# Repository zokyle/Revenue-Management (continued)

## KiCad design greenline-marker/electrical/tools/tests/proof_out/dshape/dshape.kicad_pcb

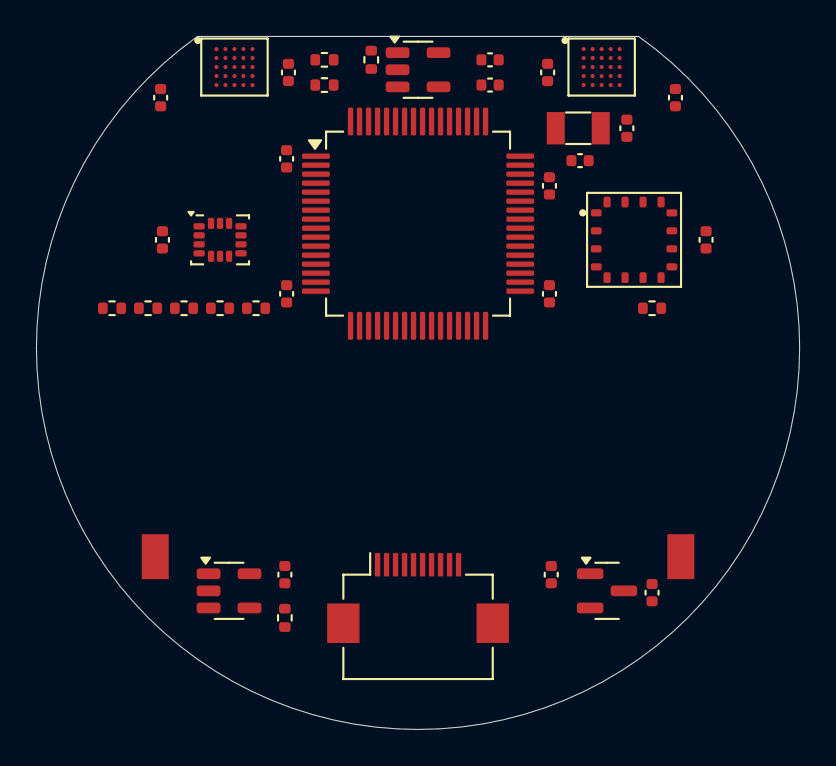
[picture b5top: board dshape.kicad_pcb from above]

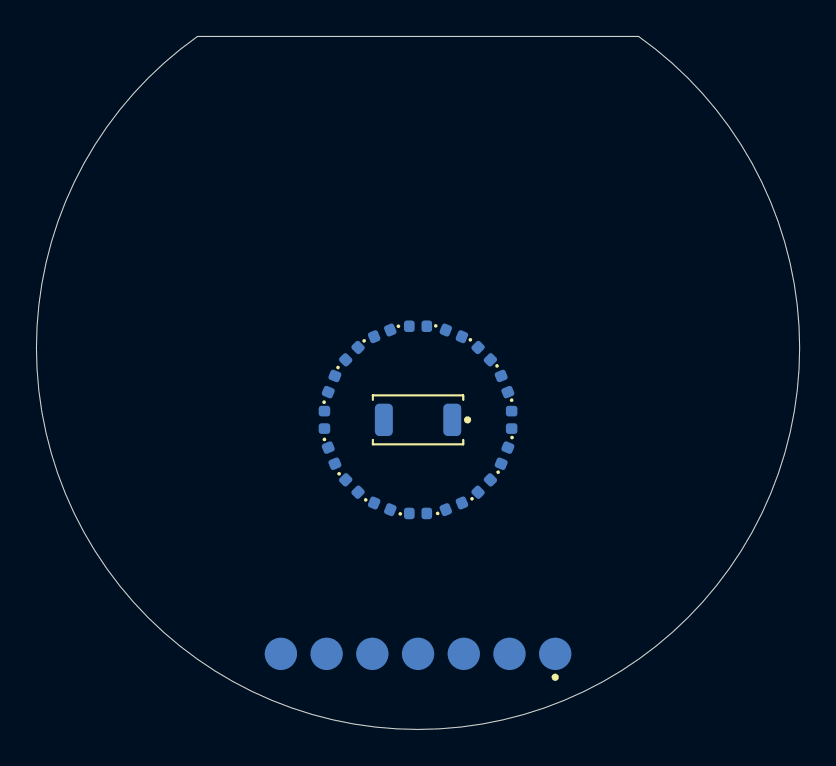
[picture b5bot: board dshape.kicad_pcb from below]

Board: 4 copper layers, 42.4 x 38.5 mm, 57 parts (18 on the bottom side), 56 nets, no tracks yet.

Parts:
BT1: BAT+; BatteryTab_1.5x2.5mm
BT2: BAT-; BatteryTab_1.5x2.5mm
C1, C2, C3, C12, C13, C16, C17: 100n; C_0402_1005Metric
C4: 4u7; C_0402_1005Metric
C5, C6, C7, C8, C9, C10, C11: 1u; C_0402_1005Metric
C14, C15: 12p; C_0402_1005Metric
D1, D3, D5, D7, D9, D11, D13, D15: LED red; LED_0402_1005Metric
D2, D4, D6, D8, D10, D12, D14, D16: LED NIR; LED_0402_1005Metric
J1: LCD FPC 10; Hirose_FH12-10S-0.5SH_1x10-1MP_P0.50mm_Horizontal
J2: Cradle pads; ContactRow_7x1.8mm_P2.54
PD1: Photodiode; Photodiode_4.8x2.5mm
R1, R2, R3, R4, R5: 68R; R_0402_1005Metric
R6, R7, R10: 2k2; R_0402_1005Metric
R8: 49k9; R_0402_1005Metric
R9: 100k; R_0402_1005Metric
U1: MCU LQFP-64; LQFP-64_10x10mm_P0.5mm
U2, U3: Camera cube; CamCube_BGA25_P0.5
U4: IMU LGA-14; LGA-14_3x2.5mm_P0.5mm_LayoutBorder3x4y
U5: Inclinometer LGA-16; LGA-16_5x5mm_P1.0mm
U7: LDO 3V0; SOT-23
U8: LDO 2V8; SOT-23-5
U9: Charger; SOT-23-5
Y1: 32.768k; Crystal_SMD_3215-2Pin_3.2x1.5mm

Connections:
+3V0: C1.1, C2.1, C3.1, C4.1, C11.1, C12.1, C13.1, J1.6, J1.7, J1.8, U1.1 (VDD), U1.19 (VDD), U1.32 (VDD), U1.48 (VDD), U1.64 (VDD), U4.5 (VDDIO), U4.8 (VDD), U5.1 (VDD), U5.2 (VDDIO), U7.2 (VOUT)
CAM_D0: U1.50 (D0), U2.B2 (D0), U3.B2 (D0)
CAM_D1: U1.51 (D1), U2.B3 (D1), U3.B3 (D1)
CAM_D2: U1.52 (D2), U2.B4 (D2), U3.B4 (D2)
CAM_D3: U1.53 (D3), U2.C2 (D3), U3.C2 (D3)
CAM_D4: U1.54 (D4), U2.C3 (D4), U3.C3 (D4)
CAM_D5: U1.55 (D5), U2.C4 (D5), U3.C4 (D5)
CAM_D6: U1.56 (D6), U2.D2 (D6), U3.D2 (D6)
CAM_D7: U1.57 (D7), U2.D3 (D7), U3.D3 (D7)
CAM_EN: R9.1, U1.44 (CAM_EN), U8.3 (EN)
CAM_HREF: U1.59 (HREF), U2.D4 (HREF), U3.D4 (HREF)
CAM_L_DVDD: C7.1, U2.D5 (DVDD)
CAM_PCLK: U1.58 (PCLK), U2.A2 (PCLK), U3.A2 (PCLK)
CAM_PWDN_L: U1.46 (PWDN_L), U2.C1 (PWDN)
CAM_PWDN_R: U1.45 (PWDN_R), U3.C1 (PWDN)
CAM_R_DVDD: C8.1, U3.D5 (DVDD)
CAM_SCL_L: R6.2, U1.62 (SCL_L), U2.B1 (SCL)
CAM_SCL_R: R7.2, U1.33 (SCL_R), U3.B1 (SCL)
CAM_SDA: R10.2, U1.49 (SDA), U2.B5 (SDA), U3.B5 (SDA)
CAM_VSYNC: U1.60 (VSYNC), U2.A3 (VSYNC), U3.A3 (VSYNC)
CAM_XVCLK: U1.61 (XVCLK), U2.A4 (XVCLK), U3.A4 (XVCLK)
CHG_PROG: R8.1, U9.5 (PROG)
CHG_STAT: U1.40 (CHG_STAT), U9.1 (STAT)
CP1: D1.2 (A), D2.1 (K), D9.1 (K), D10.2 (A), D11.2 (A), D12.1 (K), R1.2
CP1_MCU: R1.1, U1.25 (CP1)
CP2: D1.1 (K), D2.2 (A), D3.2 (A), D4.1 (K), D13.2 (A), D14.1 (K), R2.2
CP2_MCU: R2.1, U1.26 (CP2)
CP3: D3.1 (K), D4.2 (A), D5.2 (A), D6.1 (K), D11.1 (K), D12.2 (A), D15.2 (A), D16.1 (K), R3.2
CP3_MCU: R3.1, U1.27 (CP3)
CP4: D5.1 (K), D6.2 (A), D7.2 (A), D8.1 (K), D13.1 (K), D14.2 (A), R4.2
CP4_MCU: R4.1, U1.28 (CP4)
CP5: D7.1 (K), D8.2 (A), D9.2 (A), D10.1 (K), D15.1 (K), D16.2 (A), R5.2
CP5_MCU: R5.1, U1.29 (CP5)
CS_IMU: U1.5 (CS_IMU), U4.12 (CS)
CS_INC: U1.6 (CS_INC), U5.5 (CS)
GND: BT2.1, C1.2, C2.2, C3.2, C4.2, C5.2, C6.2, C7.2, C8.2, C9.2, C10.2, C11.2, C12.2, C13.2, C14.2, C15.2, C16.2, C17.2, J1.9, J1.10, J1.MP, J2.4, PD1.A, R8.2, R9.2, U1.18 (VSS), U1.31 (VSS), U1.47 (VSS), U1.63 (VSS), U2.E2 (GND1), U2.E3 (GND2), U2.E4 (GND3), U3.E2 (GND1), U3.E3 (GND2), U3.E4 (GND3), U4.2 (SDX), U4.3 (SCX), U4.6 (GND1), U4.7 (GND2), U5.3 (GND1), U5.4 (GND2), U7.1 (GND), U8.2 (GND), U9.2 (VSS)
IMU_INT: U1.7 (IMU_INT), U4.4 (INT1)
LCD_DISP: J1.5, U1.24 (LCD_DISP)
LCD_EXTCOMIN: J1.4, U1.23 (LCD_EXTCOMIN)
LCD_SCLK: J1.1, U1.20 (LCD_SCLK)
LCD_SCS: J1.3, U1.22 (LCD_SCS)
LCD_SI: J1.2, U1.21 (LCD_SI)
NRST: J2.7, U1.36 (NRST)
OSC32_IN: C14.1, U1.8 (OSC32_IN), Y1.1
OSC32_OUT: C15.1, U1.9 (OSC32_OUT), Y1.2
PD_K: PD1.K, U1.30 (PD_IN)
SPI_MISO: U1.4 (SPI_MISO), U4.1 (SDO), U5.8 (MISO)
SPI_MOSI: U1.3 (SPI_MOSI), U4.14 (SDA), U5.7 (MOSI)
SPI_SCK: U1.2 (SPI_SCK), U4.13 (SCL), U5.6 (SCK)
SWCLK: J2.6, U1.35 (SWCLK)
SWDIO: J2.5, U1.34 (SWDIO)
USB_DM: J2.2, U1.37 (USB_DM)
USB_DP: J2.3, U1.38 (USB_DP)
V2V8_CAM: C6.1, C16.1, C17.1, R6.1, R7.1, R10.1, U2.C5 (AVDD), U2.D1 (DOVDD), U3.C5 (AVDD), U3.D1 (DOVDD), U8.5 (VOUT)
VBAT: BT1.1, C5.1, C10.1, U7.3 (VIN), U8.1 (VIN), U9.3 (VBAT)
VBUS: C9.1, J2.1, U1.39 (VBUS_SENSE), U9.4 (VDD)

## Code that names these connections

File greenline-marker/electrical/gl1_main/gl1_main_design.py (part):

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VEMD8080_PAD_SIZE = 0.55

#: PROVISIONAL - every number behind the supply-chain table of NETLIST_NOTES 4.1
#: (cradle USB connector -> fuse -> spring pins -> Schottky D17 -> VBUS_D).
#: None of them was read from a data sheet.  ``charger_vin_min`` is the figure
#: docs/research/power.md records for the BQ2510x ("4.45-6.45 V operating
#: input", marked UNVERIFIED there); what the charger does below it (input
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#: STM32U585RITx in LQFP-64, pad 1 .. 64 (PINDATA; check_pinmap.py compares
#: every row with ST's STM32U585RITx.xml and with the installed KiCad symbol).
MCU_PAD_NAMES = (
    "VBAT PC13 PC14 PC15 PH0 PH1 NRST PC0 PC1 PC2 PC3 VSSA VDDA PA0 PA1 PA2 "
    "PA3 VSS VDD PA4 PA5 PA6 PA7 PC4 PC5 PB0 PB1 PB2 PB10 VCAP VSS VDD "
    "PB12 PB13 PB14 PB15 PC6 PC7 PC8 PC9 PA8 PA9 PA10 PA11 PA12 PA13 VSS VDDUSB "
    "PA14 PA15 PC10 PC11 PC12 PD2 PB3 PB4 PB5 PB6 PB7 PH3 PB8 PB9 VSS VDD").split()
assert len(MCU_PAD_NAMES) == 64


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#:   gl_pins.h), CHANGED (moved from the pin in ``was``; ``reason`` says why)
PINMAP = [
    # ---- camera port: fixed by the DCMI alternate functions (spec, PINDATA) --------------
    ("CAM_D0", "PC6", "CAM_D0", "AF", "DCMI_D0", 10, "none", CAM_OFF, S, None, ""),
    ("CAM_D1", "PC7", "CAM_D1", "AF", "DCMI_D1", 10, "none", CAM_OFF, S, None, ""),
    ("CAM_D2", "PC8", "CAM_D2", "AF", "DCMI_D2", 10, "none", CAM_OFF, S, None, ""),
    ("CAM_D3", "PC9", "CAM_D3", "AF", "DCMI_D3", 4, "none", CAM_OFF, S, None, ""),
    ("CAM_D4", "PC11", "CAM_D4", "AF", "DCMI_D4", 10, "none", CAM_OFF, S, None, ""),
    ("CAM_D5", "PB6", "CAM_D5", "AF", "DCMI_D5", 10, "none", CAM_OFF, S, None, ""),
    ("CAM_D6", "PB8", "CAM_D6", "AF", "DCMI_D6", 10, "none", CAM_OFF, S, None, ""),
    ("CAM_D7", "PB9", "CAM_D7", "AF", "DCMI_D7", 10, "none", CAM_OFF, S, None, ""),
    ("CAM_PIXCLK", "PA6", "CAM_PCLK", "AF", "DCMI_PIXCLK", 4, "none", CAM_OFF, S, None, ""),
    ("CAM_HREF", "PA4", "CAM_HREF", "AF", "DCMI_HSYNC", 10, "none", CAM_OFF, S, None, ""),
    ("CAM_VSYNC", "PB7", "CAM_VSYNC", "AF", "DCMI_VSYNC", 10, "none", CAM_OFF, S, None, ""),
    ("CAM_XVCLK", "PA8", "MCO", "AF", "RCC_MCO", 0, "none", CAM_OFF, S, None, ""),
    # ---- camera control: on the package edge that faces the cameras (pads 1-16) ----------
    ("CAM_L_SCL", "PC3", "CAM_SCL_L", "SCCB_OD", "GPIO", None, "none / 2k2 to V2V8_CAM", CAM_OFF, C, "PB3",
     "PB3 is needed for SPI1_SCK next to the flash; PC3 is the left end of the camera-facing edge"),
    ("CAM_L_PWDN", "PC2", "CAM_L_PWDN_MCU", "OUT_PP", "GPIO", None, "none / 1k series", CAM_OFF, C, "PH0",
     "PC2 sits next to CAM_L_SCL on the camera-facing edge; PH0 takes CAM_PWR_EN"),
    ("CAM_SCCB_SDA", "PC1", "CAM_SDA", "SCCB_OD", "GPIO", None, "none / 2k2 to V2V8_CAM", CAM_OFF, C, "PB5",
     "PB5 is needed for SPI1_MOSI next to the flash; PC1 is in the middle of the camera-facing edge"),
    ("CAM_R_SCL", "PC0", "CAM_SCL_R", "SCCB_OD", "GPIO", None, "none / 2k2 to V2V8_CAM", CAM_OFF, C, "PA10",
     "PA10 is on the battery-facing edge; PC0 faces the cameras, PA10 takes FLASH_CS"),
    ("CAM_R_PWDN", "PH3", "CAM_R_PWDN_MCU", "OUT_PP", "GPIO", None, "none / 10k to GND (BOOT0), 1k series", CAM_OFF, C, "PC12",
     "the BOOT0 pad must carry one signal (51 signals, 51 I/O pads). PWDN of the right camera suits it: the pad is "
     "on the edge next to that camera, the net has no pull-up (BOOT0 stays low at every reset) and a static output "
     "does not mind the 10k; the firmware's proposal, NTC_BIAS, would be loaded by it"),
    ("CAM_PWR_EN", "PH0", "CAM_EN", "OUT_PP", "GPIO", None, "none / 100k to GND", "low (rail off)", C, "PD2",
     "camera-facing edge; a static signal is the right neighbour for OSC32_OUT (pad 4); PD2 goes to the grain LEDs"),
    # ---- LCD (J1): pads 28, 29, 33 are the lower left corner, the way down to J1 -----------
    ("LCD_SCS", "PB10", "LCD_SCS", "OUT_PP", "GPIO", None, "none / 100k to GND", "low (not selected)", P, None, ""),
    ("LCD_DISP", "PB12", "LCD_DISP", "OUT_PP", "GPIO", None, "none / 100k to GND (and 200k: grain bias divider)",
     "low (display off)", C, "PB1",
     "exchanged with IMU_CS (see there): a line with a pull-DOWN is what the ROM bootloader's SPI2 chip-select "
     "input can carry without harm; pad 33 is on the way down to J1"),
    ("LCD_EXTCOMIN", "PB2", "LCD_EXTCOMIN", "AF", "LPTIM1_CH1", 1, "none", "low until LPTIM1 runs", S, None, ""),
    # ---- SPI1: flash and LCD.  MISO is fixed on PB4, so clock and data sit on its neighbours
    ("SPI1_SCK", "PB3", "SPI1_SCK", "AF", "SPI1_SCK", 5, "none", "low", C, "PA5",
     "PB3 / PB4 / PB5 are three adjacent pads on the edge that faces the flash; PA5 is on the opposite edge"),
    ("SPI1_MISO", "PB4", "SPI1_MISO", "AF", "SPI1_MISO", 5, "none", "input", S, None, ""),
    ("SPI1_MOSI", "PB5", "SPI1_MOSI", "AF", "SPI1_MOSI", 5, "none", "low", C, "PA7",
     "see SPI1_SCK"),
    ("FLASH_CS", "PA10", "FLASH_CS", "OUT_PP", "GPIO", None, "none / 100k to V2V8", "high (not selected)", C, "PA15",
     "PA10 is the ROM bootloader's USART1_RX: a pulled-up chip select is exactly the idle level it wants there, "
     "a floating charlieplex line is not. PA15 is no place for a chip select either: it is the UCPD1_CC1 pad, "
     "which gets a 5.1 kohm pull-down while PB5 (SPI1_MOSI, floating in reset) is high (PROVISIONAL)"),
    # ---- IMU on SPI2: pads 34-36 at the corner next to the IMU, chip select and interrupts on the left edge
    ("SPI2_SCK", "PB13", "SPI2_SCK", "AF", "SPI2_SCK", 5, "none", "low", P, None, ""),
    ("SPI2_MOSI", "PB15", "SPI2_MOSI", "AF", "SPI2_MOSI", 5, "none", "low", P, None, ""),
    ("SPI2_MISO", "PB14", "SPI2_MISO", "AF", "SPI2_MISO", 5, "none", "input", P, None, ""),
    ("IMU_CS", "PB1", "IMU_CS", "OUT_PP", "GPIO", None, "none / 100k to V2V8", "high (not selected)", C, "PB12",
     "PB12 is the ROM bootloader's SPI2 chip-select input and PB14 its SPI2 data output, wired to the IMU's SDO. "
     "If the ROM enables a pull-down on PB12 (the remembered AN2606 text says it does), the 100k pull-up loses, "
     "the IMU is selected and its SDO fights PB14. On PB1 (left edge, next to the IMU, no bootloader function) "
     "the pull-up always wins and SDO stays high-impedance"),
    ("IMU_INT1", "PA7", "IMU_INT1", "EXTI", "GPIO (PWR_WKUP8)", None, "none", "input", C, "PC13",
     "PA7 faces the IMU and is a wake-up pin (WKUP8); PC13 is on the far corner next to the crystal and takes "
     "VBUS_SENSE"),
    ("IMU_INT2", "PA5", "IMU_INT2", "EXTI", "GPIO", None, "none", "input", C, "PC5",
     "PA5 faces the IMU. PA5 / PA7 are the ROM bootloader's SPI1 clock and data inputs: with both driven by the "
     "IMU they always have a defined level; PC5 takes NTC_BIAS"),
    # ---- grain sensor: the corner of the package next to the LED ring ------------------------
    ("GRAIN_CP0", "PA9", "CP0_MCU", "OUT_PP", "GPIO", None, "none / 68R series", "analog (no LED lit)", C, "PC0",
     "PC0-PC3 face the cameras and carry SCCB / PWDN now; PA9, PC10, PC12, PD2 are the corner next to the "
     "LED ring"),
    ("GRAIN_CP1", "PB0", "CP1_MCU", "OUT_PP", "GPIO", None, "none / 68R series", "analog (no LED lit)", C, "PC1",
     "PC1 carries SCCB data now. The free pad at the LED corner, PA15, is the UCPD1_CC1 pad (PINDATA): a 5.1 kohm "
     "dead-battery pull-down appears on it while PB5 is high until firmware sets UCPD_DBDIS, and its output "
     "stage may be weaker than an ordinary pad's (ST's FT_c structure; both PROVISIONAL, DS13086 not read). "
     "Line 1 lights 8 of the 16 LEDs at 5 to 10 mA, so it sits on an ordinary pad instead: PB0, the nearest "
     "one with no ROM bootloader function, exchanged with CHG_STAT"),
    ("GRAIN_CP2", "PC12", "CP2_MCU", "OUT_PP", "GPIO", None, "none / 68R series", "analog (no LED lit)", C, "PC2",
     "see GRAIN_CP0"),
    ("GRAIN_CP3", "PD2", "CP3_MCU", "OUT_PP", "GPIO", None, "none / 68R series", "analog (no LED lit)", C, "PC3",
     "see GRAIN_CP0"),
    ("GRAIN_CP4", "PC10", "CP4_MCU", "OUT_PP", "GPIO", None, "none / 68R series", "analog (no LED lit)", P, None, ""),
    ("OPAMP_VINP", "PA0", "VBIAS", "ANALOG", "OPAMP1_VINP", None, "none", "analog", S, None, ""),
    ("OPAMP_VINM", "PA1", "PD_K", "ANALOG", "OPAMP1_VINM", None, "none", "analog", S, None, ""),
    ("OPAMP_VOUT", "PA3", "OPAMP_OUT", "ANALOG", "OPAMP1_VOUT / ADC1_IN8", None, "none / 150k to V2V8", "analog", S, None, ""),
    # ---- power supervision -------------------------------------------------------------------
    ("VBAT_SENSE", "PA2", "VBAT_SENSE", "ANALOG", "ADC1_IN7", None, "none", "analog", P, None, ""),
    # E1: the charger's open-drain CHG output replaces the MCP73831 STAT of gl_pins.h
    ("CHG_STAT", "PA15", "CHG_STAT", "EXTI", "GPIO", None, "none / 100k to V2V8", "input", C, "PB0",
     "exchanged with GRAIN_CP1 (see there). An INPUT is what the UCPD1_CC1 pad can carry whatever its output "
     "stage is: its reset state (JTDI, internal pull-up) agrees with the 100 kohm pull-up, and a dead-battery "
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
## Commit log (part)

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2026-04-09 Add hotel revenue management system with demand forecasting, dynamic pricing, and EBITDA optimization
    Complete system for independent hotels to optimize RevPAR through rate-driven strategies while
    maximizing EBITDA. Includes demand forecasting (decomposition + pickup model), dynamic pricing
    engine with configurable aggressiveness and rate protection, EBITDA optimizer using scipy,
    displacement analysis for group bookings, PMS integration adapters (Cloudbeds/Opera/Mews),
    web dashboard with Jinja2+HTMX+Chart.js, and seed data script with 1 year of realistic
    reservation history for a 150-room boutique hotel.
